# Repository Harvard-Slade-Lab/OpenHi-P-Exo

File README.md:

# OpenHi-P Exoskeleton
Open-source, High-torque, and Portable (OpenHi-P) hip exoskeleton

Supplementary materials for "An open-source, high-torque, and portable hip exoskeleton for physically demanding locomotion."

This repository contains the controller firmware, the host-PC human-in-the-loop optimization
software, and the hardware design files with the build guide. The study data and the MATLAB code
that reproduces the figures and statistics are Supplementary Data 1 of the paper, provided with
the article; its README gives the commands.

## Software Overview

| Runs on | Directory | Language / toolchain |
|---|---|---|
| **Host PC** (Windows): human-in-the-loop optimization | `Optimizer/` | Python, conda (`Optimizer/metcma.yml`) |
| **Exoskeleton** (STM32 microcontroller): real-time control | `Controller/` | C, STM32CubeIDE 1.17.0 |
| **Sensor nodes** (Feather M4 CAN Express, one per thigh): IMU and load-cell data to the controller | `Hardware/Electronics/Sensor-Node/firmware/` | C++, Arduino with the Adafruit SAMD core |

### Block diagram of the code

```mermaid
flowchart LR
    subgraph PC["Host PC: Optimizer/ (Python)"]
        OPT["CMA-ES optimization<br/>metabolic estimation (COSMED screen)<br/>GUI"]
    end
    subgraph MCU["STM32: Controller/ (C)"]
        LOOP["Main loop<br/>Bluetooth frames, SD log"]
        CTRL["1 kHz control interrupt<br/>gait phase, torque profile,<br/>motor current, fault checks"]
    end
    NODE["Sensor nodes<br/>IMU, load cell"]
    MOT["Actuators"]
    OPT <-->|"Bluetooth"| LOOP
    LOOP <--> CTRL
    NODE -->|"CAN1"| CTRL
    CTRL <-->|"CAN2"| MOT
```

The optimizer sends each torque profile to the controller over Bluetooth; the controller applies it
at 1 kHz from the sensor-node data and drives the actuators.

## Hardware

| CAD model | Controller board | Sensor-node carrier |
|:---:|:---:|:---:|
|  |  |  |

- `Hardware/Hip Exoskeleton Hardware Building Guide.pdf`: bill of materials, fabrication, assembly and electronics.
- `Hardware/BOM.csv`: bill of materials with the electronics, connectors and cables (unit prices in US dollars).
- `Hardware/CAD/`: SolidWorks 2022 model, drawings of the cut parts and STL files of the printed parts.
  Commercial parts (fasteners, actuators, emergency-stop switch) are not included; `Hardware/CAD/README.md`
  lists where to get them.
- `Hardware/Electronics/`: system schematic ([PDF](Hardware/Electronics/OpenHipExo_system.pdf), KiCad 10);
  KiCad and fabrication files of the controller board (`Controller-Board/`) and of the sensor-node carrier
  (`Sensor-Node/`), and the sensor-node firmware (`Sensor-Node/firmware/`).

## Controller (Firmware)

- STM32F446 firmware in C: gait phase estimation, torque profile, motor current control, CAN and
  Bluetooth communication, SD-card logging and fault checks.
- Build and flash with STM32CubeIDE 1.17.0 (building guide, "Import, build, and flash the firmware");
  host tests (need a C compiler): `bash Controller/Tests/run_tests.sh`.
- Bluetooth: the optimizer sends CRC-checked PARAMS, STOP and PING frames, and the controller
  acknowledges each (`Controller/Core/Inc/ble_protocol.h`). Use the firmware and the optimizer from the
  same release.

## Optimizer (Host PC)

- Python (conda environment `Optimizer/metcma.yml`): CMA-ES optimization of the torque profile from the
  metabolic cost measured in real time.
- Runs on Windows (screen capture of the COSMED Omnia window); the tests and the worked example also run
  on macOS and Linux.
- Run with `python main.py`; `Optimizer/README.md` gives the installation (with the Tesseract OCR
  setup), usage, metabolic estimation, tests and worked example.

## Repository Structure

- `Controller/`: STM32CubeIDE project (sources in `Core/Src/`, headers in `Core/Inc/`)
  - `main.c`: start-up, 1 kHz control interrupt and main loop; `globals.c`: shared data
  - Control: `control_logic.c` (gait phase), `torque_profile.c`, `torque_calculation.c`, `motor_control.c`
  - Communication: `can_rx_callback.c`, `imu_processing.c`, `servo_receiving.c`, `servo_sending.c` (CAN); `ble_protocol.c` (Bluetooth)
  - Safety and logging: `fault_monitor.c`, `sd_card.c`, `FATFS/`
  - Peripheral and system files generated by STM32CubeMX from `Open Hip Exo.ioc` (`can.c`, `tim.c`, `usart.c`, ...)
  - `Tests/`: host tests (`run_tests.sh`): protocol parser, fault monitor, torque profile, phase mapping
- `Hardware/`: see Hardware above.
- `Optimizer/`: host-PC optimization (Python)
  - `main.py`: entry point (GUI, Bluetooth, metabolic data, controller link)
  - `hiloMetCmaController.py`, `cma_optimizer.py`: optimization loop and CMA-ES (pycma 3.4.0)
  - `metabolics_collect.py`, `metabolics_extract.py`: metabolic data from the COSMED screen
  - `bleFunctions.py`: Bluetooth link
  - `serialPlotter.py`, `param_utils.py`, `timer_manager.py`: plots and utilities
  - `metcma.yml`: conda environment; `tests/`: tests and the worked example

## Citation

To cite this repository, use `CITATION.cff` ("Cite this repository" on GitHub). Release v1.0.0 is archived at Zenodo.

## License

This project is released under the MIT License; see `LICENSE`. The license covers
the firmware in `Controller/Core/` and its host tests in `Controller/Tests/`, the
host-PC optimization code in `Optimizer/`, and the hardware design files created for
this project: `Hardware/CAD/`, `Hardware/Electronics/`
(including the sensor-node firmware) and `Hardware/BOM.csv`.

Three exceptions:

- Third-party components vendored under `Controller/Drivers/` and
  `Controller/Middlewares/` remain under their own licenses. CMSIS is Apache-2.0,
  the STM32F4xx HAL driver is BSD-3-Clause, and FatFs is under the ChaN one-clause
  BSD license. CMSIS and the HAL driver carry their own LICENSE.txt; the FatFs terms
  are stated in the headers of its source files.
- Commercial off-the-shelf CAD models are not redistributed here and are not covered
  by this license; see `Hardware/CAD/README.md`.
- Symbols, footprints and 3D models from the KiCad libraries, used in the board files,
  the board images and the board models in `Hardware/CAD/`, keep the license of the KiCad libraries.

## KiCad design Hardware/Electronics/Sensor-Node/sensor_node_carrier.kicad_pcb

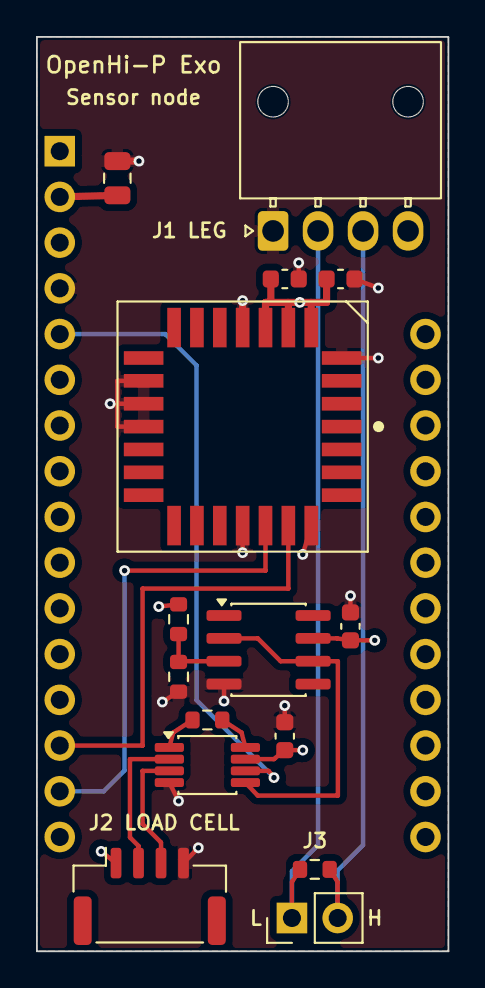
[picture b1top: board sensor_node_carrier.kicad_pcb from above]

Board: 4 copper layers, 22.9 x 50.8 mm, 16 parts (0 on the bottom side), 14 nets.

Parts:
A1: Feather M4 CAN Express; Adafruit_Feather_Socketed
C1, C2, C3, C4: 100n; C_0603_1608Metric
C5: 10u; C_0805_2012Metric
J1: Leg cable; Molex_Nano-Fit_105313-xx04_1x04_P2.50mm_Horizontal
J2: Load cell; JST_GH_SM04B-GHS-TB_1x04-1MP_P1.25mm_Horizontal
J3: CAN to Feather; PinHeader_1x02_P2.54mm_Vertical
R1: 267 0.1%; R_0603_1608Metric
R2: 16.2k 0.1%; R_0603_1608Metric
R3: 28.0k 0.1%; R_0603_1608Metric
R4: 120; R_0603_1608Metric
U1: MTi-3; Xsens_MTi-1_series
U2: INA333; VSSOP-8_3x3mm_P0.65mm
U3: OPA333; SOIC-8_3.9x4.9mm_P1.27mm

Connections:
+3V3: A1.2, C1.1, C2.1, C3.1, C4.1, C5.1, J2.1, R2.1, U1.5, U1.6, U1.7, U2.7, U3.7
+5V: A1.26, J1.4
/CAN1_H: J1.3, J3.2, R4.2
/CAN1_L: J1.2, J3.1, R4.1
/IMU_RX: A1.15, U1.23
/IMU_TX: A1.14, U1.24
/LC_OUT: A1.5, U2.6
/LC_SIG_N: J2.2, U2.2
/LC_SIG_P: J2.3, U2.3
/RG_A: R1.1, U2.1
/RG_B: R1.2, U2.8
/VREF: U2.5, U3.2, U3.6
/VREF_DIV: R2.2, R3.1, U3.3
GND: A1.4, C1.2, C2.2, C3.2, C4.2, C5.2, J1.1, J2.4, R3.2, U1.4, U1.8, U1.13, U1.14, U1.15, U1.22, U1.25, U2.4, U3.4

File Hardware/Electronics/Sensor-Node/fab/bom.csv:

"References","Quantity","Value","Manufacturer part number","Footprint","Description"
"C1-C4","4","100n","0603 X7R 100 nF 16 V","Capacitor_SMD:C_0603_1608Metric","Decoupling of U2 (INA333),Decoupling of U3 (OPA333),Decoupling of the MTi-3 VDD,Decoupling of the MTi-3 VDDIO"
"C5","1","10u","0805 X5R 10 uF 10 V","Capacitor_SMD:C_0805_2012Metric","3.3 V bulk capacitor"
"J1","1","Leg cable","Molex 105313-1104","Connector_Molex:Molex_Nano-Fit_105313-xx04_1x04_P2.50mm_Horizontal","Leg cable (CBL-4, node branch): 1 GND, 2 CAN1_L, 3 CAN1_H, 4 +5V. Molex Nano-Fit header, 1 x 4, right angle; mating receptacle housing 105307 series (1 x 4) with the 105300-series terminals of CON-5"
"J2","1","Load cell","JST SM04B-GHS-TB","Connector_JST:JST_GH_SM04B-GHS-TB_1x04-1MP_P1.25mm_Horizontal","Load cell (ELE-2): 1 EXC+, 2 SIG-, 3 SIG+, 4 EXC-. JST GH, right angle; mating housing GHR-04V-S with SSHL-002T-P0.2 contacts"
"J3","1","CAN to Feather","Two wires soldered into the holes (no header: J3 is under the Feather)","Connector_PinHeader_2.54mm:PinHeader_1x02_P2.54mm_Vertical","Two wires to the CAN terminals of the Feather M4 CAN Express: 1 CAN L, 2 CAN H"
"R1","1","267 0.1%","0603 thin film 267 ohm 0.1%","Resistor_SMD:R_0603_1608Metric","Gain resistor RG of the INA333"
"R2","1","16.2k 0.1%","0603 thin film 16.2 kohm 0.1%","Resistor_SMD:R_0603_1608Metric","Reference divider, top (3.3 V)"
"R3","1","28.0k 0.1%","0603 thin film 28.0 kohm 0.1%","Resistor_SMD:R_0603_1608Metric","Reference divider, bottom: 3.3 V x 28.0 / 44.2 = 2.09 V"
"R4","1","120","0603 120 ohm 1%","Resistor_SMD:R_0603_1608Metric","CAN1 bus-end terminator; leave it out if the Feather's own CAN terminator stays connected"
"U2","1","INA333","INA333AIDGKR","Package_SO:VSSOP-8_3x3mm_P0.65mm","Instrumentation amplifier of the load-cell bridge; gain 1 + 100 kohm / RG = 375.53"
"U3","1","OPA333","OPA333AID","Package_SO:SOIC-8_3.9x4.9mm_P1.27mm","Voltage follower: buffers the 2.09 V output reference of the amplifier"

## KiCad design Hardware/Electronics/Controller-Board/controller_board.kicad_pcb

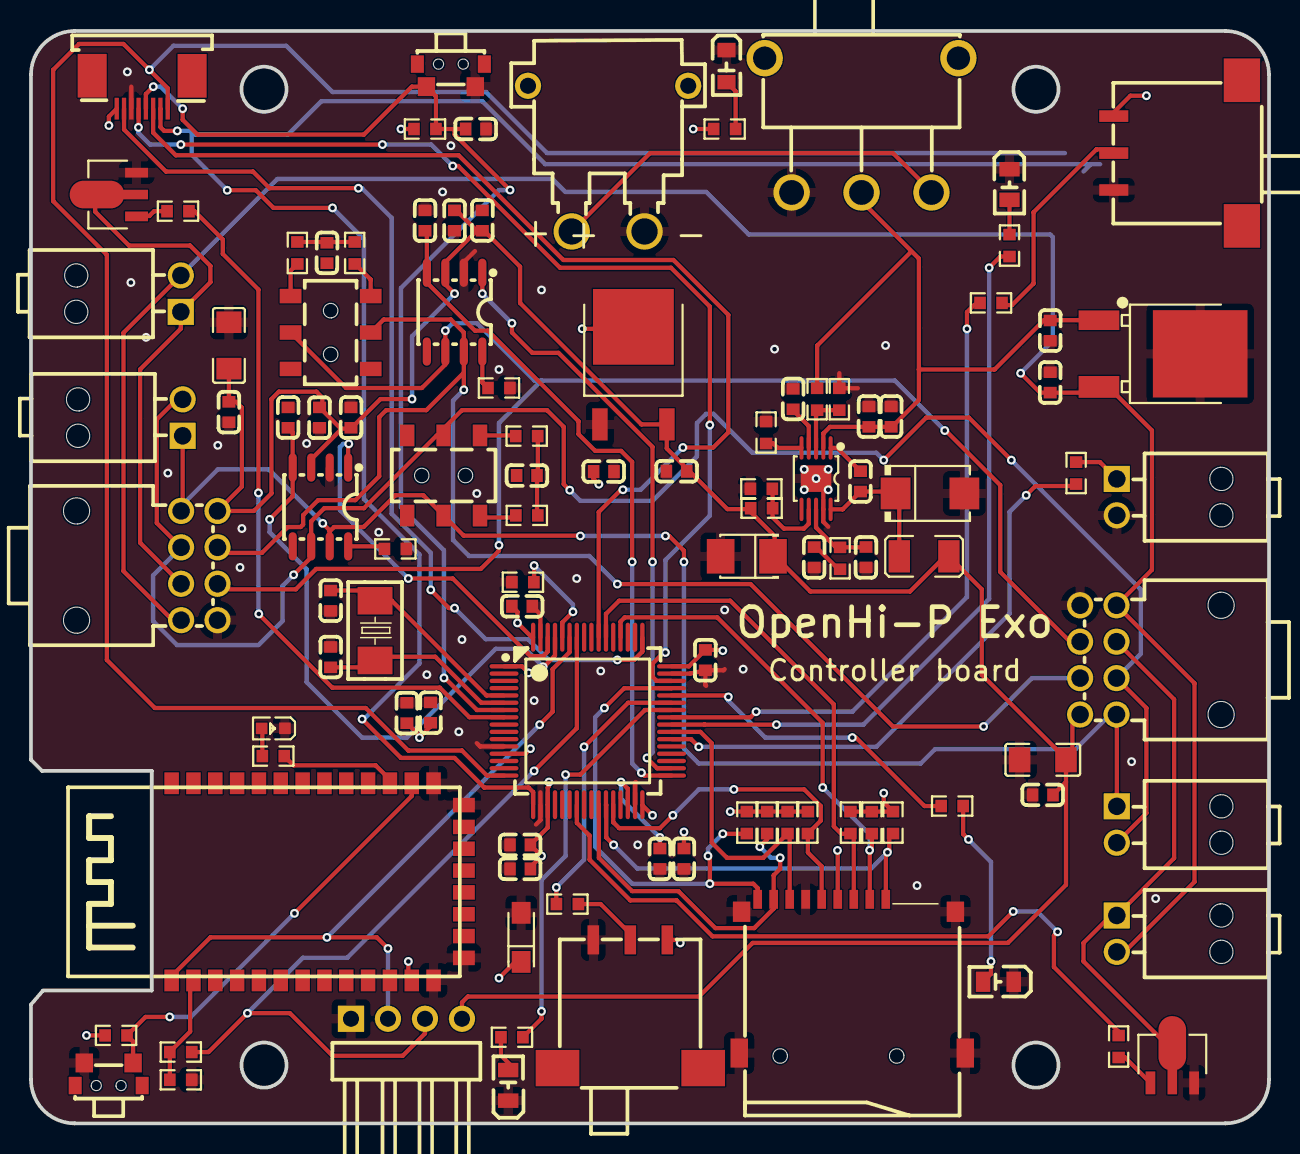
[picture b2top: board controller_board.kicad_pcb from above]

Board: 4 copper layers, 85.0 x 75.0 mm, 104 parts (0 on the bottom side), 72 nets.

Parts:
(OFF)DATA_LOG(ON): 5FS1S102MZRES; SW-SMD_DAILYWELL_5FS1S102MZRES
(OFF)POWER(ON): SS-12D11G4R; SW-TH_SS-12D11G4R
(ON)CONTROL(OFF): 5FS1S102MZRES; SW-SMD_DAILYWELL_5FS1S102MZRES
BATTERY-CON: XT30PW-M; CONN-TH_XT30PW-M
BLERESET: TS24CA; SW-SMD_TS24CA
C1, C8: 4.7 uF; C0603
C2, C3, C4, C5, C6, C9, C15, C21, C26, C27, C29, C31: 100 nF; C0603
C7: 1 uF; C0603
C10, C11: 20 pF; C0603
C12, C13: 2.2 uF; C0603
C14: 10 nF; C0603
C16, C24, C35: 4.7 nF; C0603
C17: 33 pF; C0603
C18: 100 uF; CAP-SMD_L3.5-W2.8-FD
C19, C20: 10 uF; C0603
C22, C34: 47 uF; C0603
C23, C32: 15 pF; C0603
C25: 100 nF; CAP-SMD_L3.2-W1.6-RD
C28, C30: 220 uF; C1206
C36: 330 nF; C0603
CAN1, CAN2: MS-22C01-G010; SW-SMD_6P-L7.2-W3.5-P2.50-LS6.0-TL
CONTROL_MODE_LED: NCD0805G1; LED0805-R-RD
D1: B360B-13-F; SMB_L4.6-W3.6-LS5.3-RD
DATA_LOG_LED: NCD0805G1; LED0805-R-RD
H1: PZ254R-11-04P; HDR-TH_4P-P2.54-H-M-W10.4
L1: 22 uH; L1210
LED1: NCD0805R1; LED0805-RD_RED
LED2: D-060306B1; LED0603-RD
LEFT: 1053141108; CONN-TH_8P-P2.50_MOLEX_1053141108
NOT_USED1, NOT_USED2, NOT_USED3, NOT_USED4, NOT_USED5: 1053131102; CONN-TH_2P-P2.50_MOLEX_1053131202
Q1, Q2: D882 Y (hFE 160-320); SOT-89-3_L4.5-W2.5-P1.50-LS4.2-BR
R1, R2, R8, R10, R11, R12, R13, R14, R15, R16, R22, R24, R26, R33, R35: 10k ohm; R0603
R3: 332k ohm; R0603
R4, R7: 56k ohm; R0603
R5: 237k ohm; R0603
R6: 20k ohm; R0603
R9, R17, R23, R25: 8.2k ohm; R0603
R29: 47k ohm; R0603
R30, R31, R40, R41: 1k ohm; R0603
R32: 2k ohm; R0603
R36, R37, R38, R39: 60 ohm; R0603
RESET_SW: TS24CA; SW-SMD_TS24CA
RIGHT: 1053141108; CONN-TH_8P-P2.50_MOLEX_1053141108
SDCARD: TF-01A; TF-SMD_TF-01A
SD_CD_LED: NCD0805G1; LED0805-R-RD
U1: STM32F446RET6; LQFP-64_L10.0-W10.0-P0.50-LS12.0-BL
U2: TPS54240DGQR; MSOP-10_L3.0-W3.0-P0.50-LS5.0-BL-EP
U3: NCV1117DT33T5G; TO-252-3_L6.5-W5.8-P4.58-BR
U4, U6: TJA1051T/CM,118; SOIC-8_L5.0-W4.0-P1.27-LS6.1-BL
U5: HM-10
U7: L78M05ABDT-TR; TO-252-2_L6.5-W6.1-P4.58-LS10.0-TL
UPLOAD/DEBUG: AFC07-S08FCC-00; FPC-SMD_AFC07-S08FCC-00
X1: 8 MHz; OSC-SMD_L5.0-W3.2

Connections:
$6N12578: LED1.2, R9.2
$6N17661: R3.1, R4.2, U2.3
$6N17710: C14.2, U2.4
$6N17734: R5.2, U2.5
$6N18318: C17.2, R6.2, U2.8
$6N18484: C16.2, R6.1
$6N18681: C15.2, U2.1
$7N22964: NOT_USED3.1, R33.1
$7N28780: Q1.1, R40.2
$7N28928: Q2.1, R41.2
$8N524: DATA_LOG_LED.1, R23.2
$8N526: CONTROL_MODE_LED.1, R25.2
$8N10126: (ON)CONTROL(OFF).2, R24.1
$8N10185: (OFF)DATA_LOG(ON).2, R22.1
$9N2260: R17.2, SD_CD_LED.1
$11N1717: R1.1, U1.60
$12N1241: R26.2, U4.8
$12N9535: LED2.2, R29.2
$12N9537: R29.1, U5.24
$12N9624: BLERESET.3, R30.1, U5.23
$12N13556: R31.1, R32.2, U5.2
$12N19305: R35.2, U6.8
$12N19699: C24.1, R36.2, R37.2
$12N19803: CAN2.4, R37.1
$12N19809: CAN2.1, R36.1
$12N20147: CAN1.4, R39.1
$12N20156: CAN1.1, R38.1
$12N20165: C35.1, R38.2, R39.2
+3.3V: (OFF)DATA_LOG(ON).1, (ON)CONTROL(OFF).1, C1.2, C2.2, C3.2, C4.2, C5.2, C6.1, C7.1, C19.1, C25.1, R2.2, R9.1, R10.2, R11.2, R12.2, R13.2, R14.2, R15.2, R16.2, R30.2, SDCARD.4, U1.1, U1.13, U1.19, U1.32, U1.48, U1.64, U3.2, U5.12, UPLOAD/DEBUG.8
+5V: C18.1, C20.1, C21.2, C22.2, C27.2, C28.2, C29.2, C30.2, C31.2, C34.2, H1.4, L1.1, LEFT.4, R7.2, RIGHT.4, U3.3, U4.3, U6.3
BATTERY: (OFF)POWER(ON).3, BATTERY-CON.2
CAN1_H: CAN1.2, LEFT.8, NOT_USED2.1, NOT_USED4.1, RIGHT.8, U6.7
CAN1_L: CAN1.5, LEFT.7, NOT_USED2.2, NOT_USED4.2, RIGHT.7, U6.6
CAN1_RX: C32.2, U1.61, U6.4
CAN1_TX: U1.62, U6.1
CAN2_H: CAN2.2, LEFT.3, RIGHT.3, U4.7
CAN2_L: CAN2.5, LEFT.2, RIGHT.2, U4.6
CAN2_RX: C23.2, U1.33, U4.4
CAN2_TX: U1.34, U4.1
CONTROL_MODE: R24.2, U1.41
CONTROL_MODE_LED: R25.1, U1.40
DATA_LOG: R22.2, U1.43
DATA_LOG_LED: R23.1, U1.42
GND: (OFF)DATA_LOG(ON).3, (OFF)POWER(ON).1, (ON)CONTROL(OFF).3, BATTERY-CON.1, BLERESET.4, C1.1, C2.1, C3.1, C4.1, C5.1, C6.2, C7.2, C8.1, C9.2, C10.2, C11.1, C12.1, C13.1, C14.1, C16.1, C17.1, C18.2, C19.2, C20.2, C21.1, C22.1, C23.1, C25.2, C26.2, C27.1, C28.1, C29.1, C30.1, C31.1, C32.1, C34.1, C36.2, CONTROL_MODE_LED.2, D1.2, DATA_LOG_LED.2, H1.1, LED1.1, LED2.1, LEFT.1, NOT_USED3.2, Q1.3, Q2.3, R1.2, R4.1, R5.1, R8.1, R26.1, R32.1, R35.1, RESET_SW.4, RIGHT.1, SDCARD.6, SDCARD.10, SDCARD.11, SDCARD.12, SDCARD.13, SD_CD_LED.2, U1.12, U1.18, U1.31, U1.47, U1.63, U2.9, U2.11, U3.1, U4.2, U5.13, U5.14, U5.21, U5.22, U6.2, U7.4, UPLOAD/DEBUG.6
NRST: C9.1, R2.1, RESET_SW.3, U1.7, UPLOAD/DEBUG.4
unnamed: LEFT.6, NOT_USED1.1, Q1.2
unnamed: NOT_USED5.1, Q2.2, RIGHT.6
unnamed: R33.2, U1.38
unnamed: R40.1, U1.8
unnamed: R41.1, U1.23
unnamed: C26.1, LEFT.5, NOT_USED1.2, NOT_USED5.2, RIGHT.5, U7.3
PH: C15.1, D1.1, L1.2, U2.10
RCC_OSC_IN: C10.1, U1.5, X1.2
RCC_OSC_OUT: C11.2, U1.6, X1.1
SDIO_CD: R16.1, SDCARD.9, U1.45
SDIO_CD_LED: R17.1, U1.44
SDIO_CLK: R10.1, SDCARD.5, U1.28
SDIO_CMD: R11.1, SDCARD.3, U1.54
SDIO_D0: R15.1, SDCARD.7, U1.39
SDIO_D1: R14.1, SDCARD.8, U1.26
SDIO_D2: R13.1, SDCARD.1, U1.27
SDIO_D3: R12.1, SDCARD.2, U1.52
SWCLK: U1.49, UPLOAD/DEBUG.7
SWDIO: U1.46, UPLOAD/DEBUG.5
SWO: U1.55, UPLOAD/DEBUG.3
UART_BLE_RX: H1.2, U1.59, U5.1
UART_BLE_TX: H1.3, R31.2, U1.58
UART_ST_RX: U1.17, UPLOAD/DEBUG.2
UART_ST_TX: U1.16, UPLOAD/DEBUG.1
VCAP: C8.2, U1.30
VCC: (OFF)POWER(ON).2, C12.2, C13.2, C36.1, R3.2, U2.2, U7.1
VSNS: R7.1, R8.2, U2.7

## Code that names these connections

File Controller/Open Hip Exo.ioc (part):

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Mcu.Name=STM32F446R(C-E)Tx
Mcu.Package=LQFP64
Mcu.UserName=STM32F446RETx
PA10.Signal=GPIO_Input
PA11.Signal=GPIO_Output
PA12.Signal=GPIO_Input
PA13.GPIOParameters=GPIO_Label
PA13.GPIO_Label=TMS
PA13.Mode=Serial_Wire
PA13.Signal=SYS_JTMS-SWDIO
PA14.GPIOParameters=GPIO_Label
PA14.GPIO_Label=TCK
PA14.Mode=Serial_Wire
PA14.Signal=SYS_JTCK-SWCLK
PA2.GPIOParameters=GPIO_ModeDefaultPP,GPIO_Speed,GPIO_PuPd
PA2.GPIO_ModeDefaultPP=GPIO_MODE_AF_PP
PA2.GPIO_PuPd=GPIO_NOPULL
PA2.GPIO_Speed=GPIO_SPEED_FREQ_VERY_HIGH
PA2.Mode=Asynchronous
PA2.Signal=USART2_TX
PA3.GPIOParameters=GPIO_ModeDefaultPP,GPIO_Speed,GPIO_PuPd
PA3.GPIO_ModeDefaultPP=GPIO_MODE_AF_PP
PA3.GPIO_PuPd=GPIO_NOPULL
PA3.GPIO_Speed=GPIO_SPEED_FREQ_VERY_HIGH
PA3.Mode=Asynchronous
PA3.Signal=USART2_RX
PA8.Signal=GPIO_Input
PA9.Signal=GPIO_Output
PB12.Mode=CAN_Activate
PB12.Signal=CAN2_RX
PB13.Mode=CAN_Activate
PB13.Signal=CAN2_TX
PB2.Mode=SD_1_bit
PB2.Signal=SDIO_CK
PB3.GPIOParameters=GPIO_Label
PB3.GPIO_Label=SWO
PB3.Signal=SYS_JTDO-SWO
PB6.Mode=Asynchronous
PB6.Signal=USART1_TX
PB7.Mode=Asynchronous
PB7.Signal=USART1_RX
PB8.Mode=CAN_Activate
PB8.Signal=CAN1_RX
PB9.Mode=CAN_Activate
PB9.Signal=CAN1_TX
PC8.Mode=SD_1_bit
PC8.Signal=SDIO_D0
PC9.Signal=GPIO_Output
PD2.Mode=SD_1_bit
PD2.Signal=SDIO_CMD
PH0-OSC_IN.Mode=HSE-External-Oscillator
PH0-OSC_IN.Signal=RCC_OSC_IN
PH1-OSC_OUT.Mode=HSE-External-Oscillator
PH1-OSC_OUT.Signal=RCC_OSC_OUT
RCC.HSE_VALUE=8000000
RCC.SYSCLKFreq_VALUE=168000000
RCC.SYSCLKSource=RCC_SYSCLKSOURCE_PLLRCLK
board=NUCLEO-F446RE
boardIOC=true
